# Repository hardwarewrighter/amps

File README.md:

# Amplifier bench projects

This repository collects small audio amplifier circuits, SPICE simulations, and bench build guides. The first hardware build is a 5 V mono amplifier with an LM358P driving a 2N2222/2N2907-family push-pull output stage. It has a board-mounted volume control and an eight-pin interface shared with a wired PAM8403-style carrier. The mono build uses the left channel. The harness provides separate speaker returns for a future stereo board.

## Start with the 2N2222 amplifier

The [build guide](circuits/2n2222/index.html) includes the parts list, breadboard layout, bench test steps, and both sides of the single-sided through-hole PCB. Open it directly in a browser or serve it from the repository root.

```sh
python -m http.server 8765 --bind 127.0.0.1 --directory circuits/2n2222
```

Open [http://localhost:8765/](http://localhost:8765/). Start with the 8.2 Ω dummy load, then repeat the bench checks after soldering. The PCB has passed KiCad design rule checks. The build guide gives simulated reference values for the physical tests.

- [KiCad PCB](circuits/2n2222/push-pull.kicad_pcb)
- [SPICE model](circuits/2n2222/push-pull.cir), runnable with `ngspice -b circuits/2n2222/push-pull.cir`

## Documentation and reference designs

- [Experiment plan](docs/plan.md) for comparing transistor pairs, op-amp drivers, and integrated amplifiers.
- [Research notes](docs/research.txt) and [follow-up notes](docs/research2.txt) for the design background.
- [Netlist notes](net/NOTES.txt) and [amplifier choices](net/CHOICES.txt) for model assumptions and circuit options.
- [Parts lists](bom/README.txt) and [simulation comparison](reports/index.html).
- [LM386 reference build](circuits/lm386-simple/README.txt) and [tone-control tool](tools/tone-control/README.txt).
- [Change history](CHANGES.md).

## Copyright and license

Copyright (c) 2026 Michael A Wright. See [COPYRIGHT](COPYRIGHT).

The project is licensed under the [MIT License](LICENSE).

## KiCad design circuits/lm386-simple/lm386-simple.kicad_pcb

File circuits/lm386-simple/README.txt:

Open lm386-simple.kicad_sch in KiCad Schematic Editor, or open
lm386-simple.kicad_pro in the KiCad project manager.

All ten physical components are placed and wired. KiCad 10.0.7 ERC:
zero errors, zero warnings. Exported pin connectivity was checked against
the intended circuit, including the positive side of C4 facing U1 pin 5.

lm386-simple.pdf is the printable schematic.
lm386-simple.kicad_pcb is a placed, UNROUTED learning board with footprints
and net connections. It is not ready for fabrication. Footprints are
provisional; check sizes against your actual capacitors/connectors first.
Use Update PCB from Schematic (F8) after editing the schematic.

This drawing uses 220uF output coupling and 47nF in the RC network, standard
values replacing 250uF/50nF in the earlier netlist. C3 and C4 are polarized.
Pins 1/7/8 are intentionally open. Supply is single +6 V; load is an external
8-ohm speaker at J3. This has no volume control; start with a small input.

The graphical project is for drawing/PCB exploration. Simulation sources
and a KiCad simulation model have not been attached to its symbols.
For the corresponding standalone ngspice example, run:
  ngspice circuits/lm386-simple/lm386-simple.cir
That uses the same approximate educational model as the earlier LM386 deck;
it does not validate power, distortion, stability or thermal performance.

Project-local library tables refer to the installed Arch KiCad libraries.
Embedded symbols allow the schematic to display without external symbols.

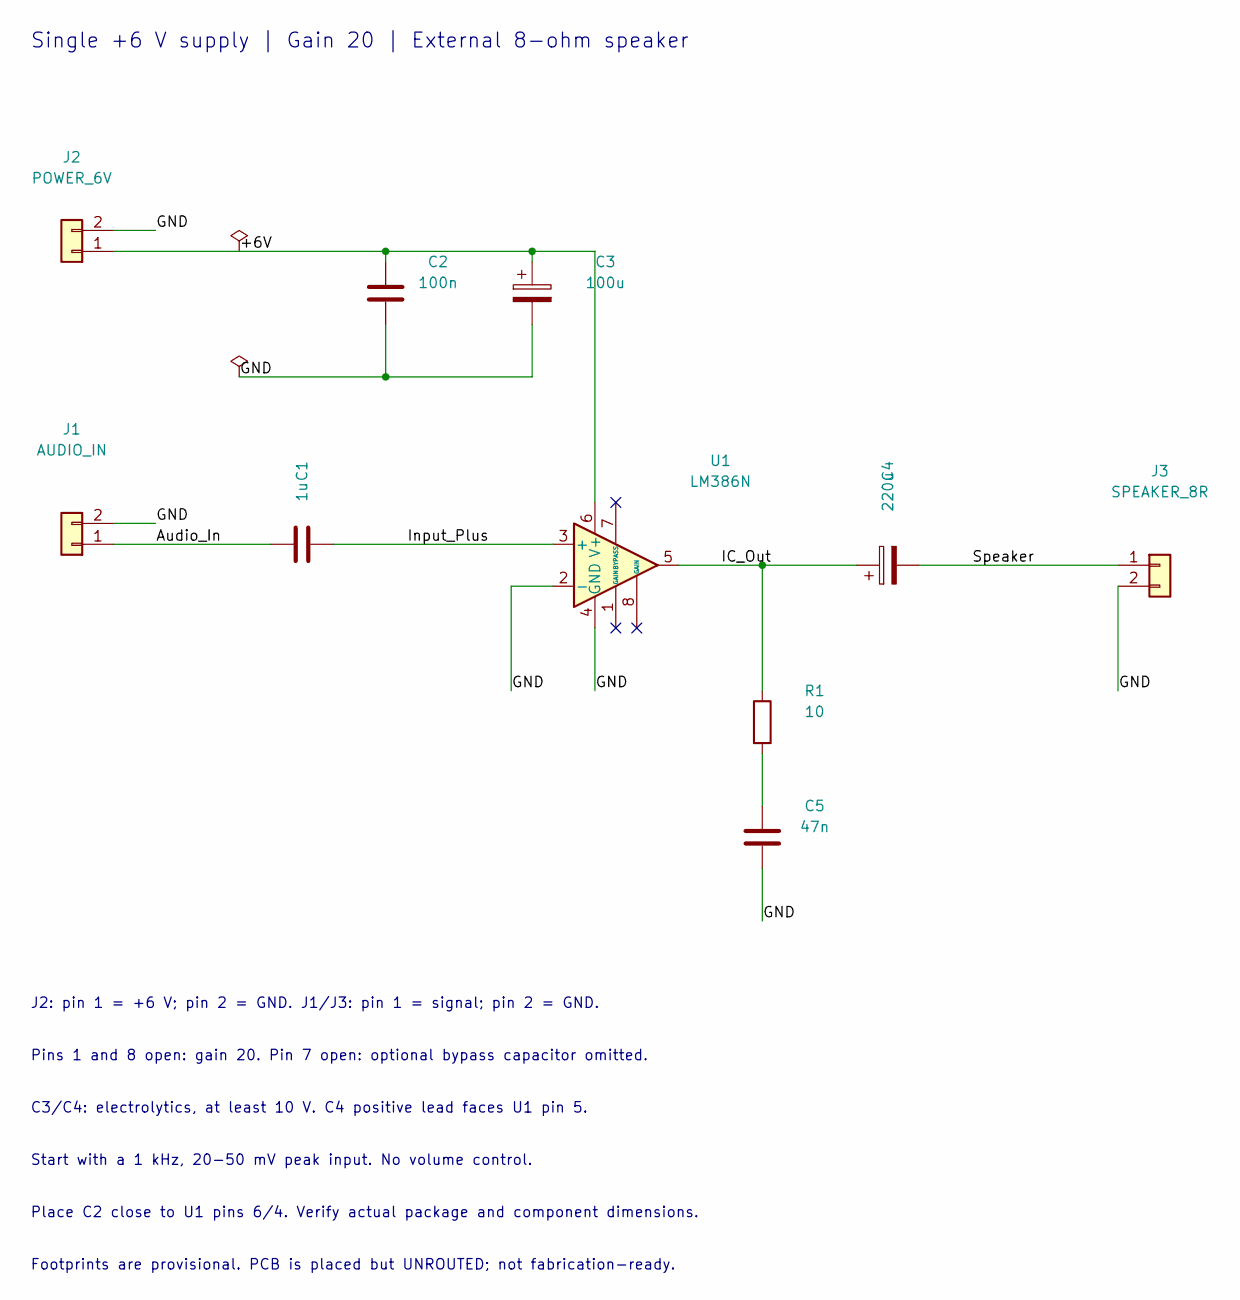
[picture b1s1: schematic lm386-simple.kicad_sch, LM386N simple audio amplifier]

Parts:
C1: 1u; C_Disc_D5.0mm_W2.5mm_P5.00mm
C2: 100n; C_Disc_D5.0mm_W2.5mm_P5.00mm
C3: 100u; CP_Radial_D6.3mm_P2.50mm
C4: 220u; CP_Radial_D6.3mm_P2.50mm
C5: 47n; C_Disc_D5.0mm_W2.5mm_P5.00mm
J1: AUDIO_IN; PinHeader_1x02_P2.54mm_Vertical
J2: POWER_6V; PinHeader_1x02_P2.54mm_Vertical
J3: SPEAKER_8R; PinHeader_1x02_P2.54mm_Vertical
R1: 10; R_Axial_DIN0207_L6.3mm_D2.5mm_P7.62mm_Horizontal
U1: LM386N; DIP-8_W7.62mm

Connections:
/+6V: C2.1, C3.1, J2.1, U1.6 (V+)
/Audio_In: C1.1, J1.1
/GND: C2.2, C3.2, C5.2, J1.2, J2.2, J3.2, U1.2 (-), U1.4 (GND)
/IC_Out: C4.1, R1.1, U1.5
/Input_Plus: C1.2, U1.3 (+)
/Speaker: C4.2, J3.1
unnamed: C5.1, R1.2

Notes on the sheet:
Single +6 V supply | Gain 20 | External 8-ohm speaker
J2: pin 1 = +6 V; pin 2 = GND. J1/J3: pin 1 = signal; pin 2 = GND.
Pins 1 and 8 open: gain 20. Pin 7 open: optional bypass capacitor omitted.
C3/C4: electrolytics, at least 10 V. C4 positive lead faces U1 pin 5.
Start with a 1 kHz, 20-50 mV peak input. No volume control.
Place C2 close to U1 pins 6/4. Verify actual package and component dimensions.
Footprints are provisional. PCB is placed but UNROUTED; not fabrication-ready.

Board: 2 copper layers, 10 parts (0 on the bottom side), 7 nets, no tracks yet.

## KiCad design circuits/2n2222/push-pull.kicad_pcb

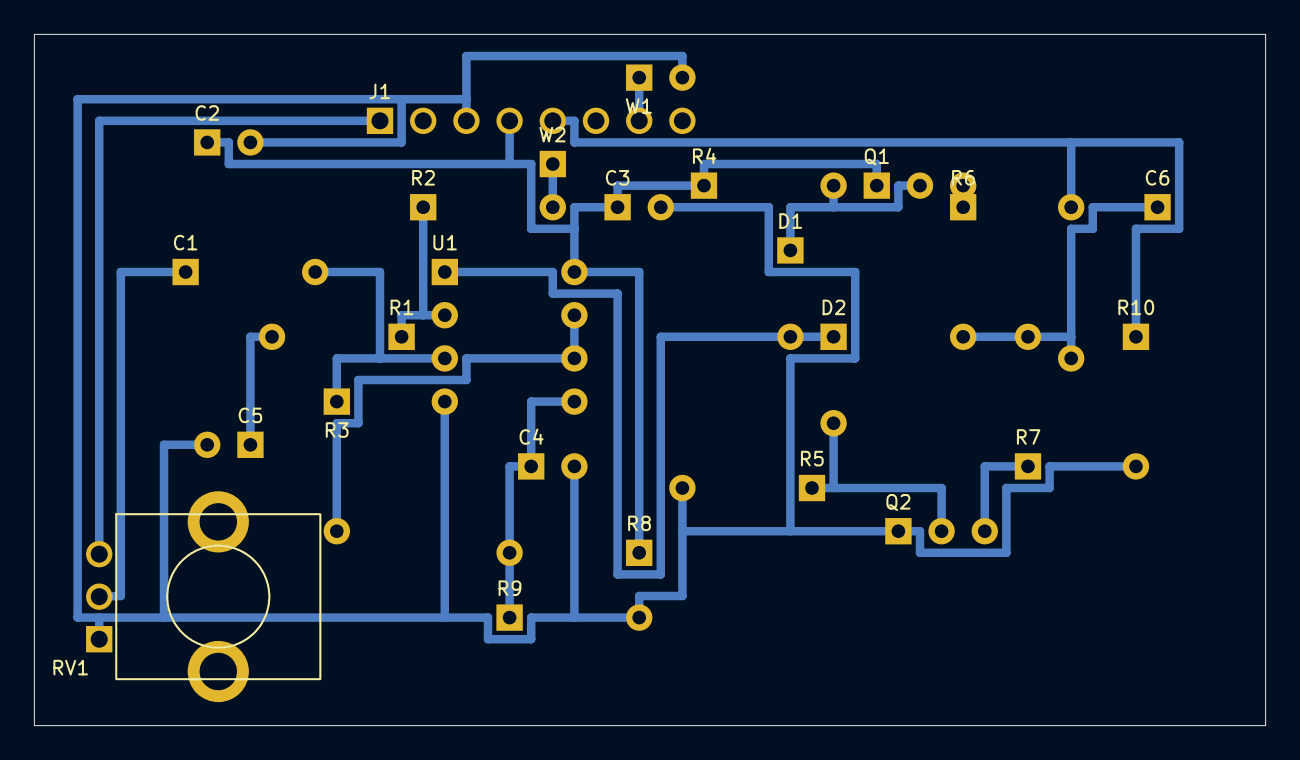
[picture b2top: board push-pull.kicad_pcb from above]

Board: 2 copper layers, 72.4 x 40.6 mm, 25 parts (0 on the bottom side), 18 nets.

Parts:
C1: C1
C2: C2
C3: C3
C4: C4
C5: C5
C6: C6
D1: D1
D2: D2
J1: J1
Q1: Q1
Q2: Q2
R1: R1
R2: R2
R3: R3
R4: R4
R5: R5
R6: R6
R7: R7
R8: R8
R9: R9
R10: R10
RV1: RV1
U1: U1
W1: W1
W2: W2

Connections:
+5: C2.1, C3.1, J1.4, Q1.1, R4.1, R8.1, U1.8
ACREF: C5.1, R1.2
BN: D1.1, Q1.2, R4.2
BP: D2.2, Q2.2, R5.1
BUF: R3.2, U1.6, U1.7
DRV: D1.2, D2.1, U1.1
EN: Q1.3, R6.1
EP: Q2.3, R7.1
FB: R1.1, R2.1, U1.2
GND: C2.2, C3.2, C4.2, C5.2, J1.3, Q2.1, R5.2, R9.2, R10.2, RV1.1, U1.4, W1.2
L+: C6.2, J1.5, R10.1
L-: J1.7, W1.1
LIN: J1.1, RV1.3
MID: C4.1, R8.2, R9.1, U1.5
OUT: C6.1, R6.2, R7.2, W2.2
PLUS: C1.2, R3.1, U1.3
SENSE: R2.2, W2.1
VOL: C1.1, RV1.2

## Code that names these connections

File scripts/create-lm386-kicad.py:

#!/usr/bin/env python3
"""Generate the LM386 learning schematic from installed KiCad library symbols."""
from pathlib import Path
import json
import math
import re
import uuid

ROOT=Path(__file__).resolve().parent.parent
OUT=ROOT/'circuits/lm386-simple'
OUT.mkdir(parents=True,exist_ok=True)
NAME='lm386-simple'
uid=lambda: str(uuid.uuid4())
q=lambda s: json.dumps(str(s))
root_uuid=uid()

def extract(library,name):
    data=Path('/usr/share/kicad/symbols',library+'.kicad_sym').read_text()
    start=data.index('(symbol '+q(name)+'\n')
    depth=0; quoted=False; escaped=False
    for i in range(start,len(data)):
        c=data[i]
        if quoted:
            if escaped: escaped=False
            elif c=='\\': escaped=True
            elif c=='"': quoted=False
        elif c=='"': quoted=True
        elif c=='(': depth+=1
        elif c==')':
            depth-=1
            if depth==0:
                return data[start:i+1].replace('(symbol '+q(name), '(symbol '+q(library+':'+name),1)
    raise ValueError(name)

libraries=[('Amplifier_Audio','LM386'),('Device','C'),('Device','C_Polarized'),('Device','R'),('Connector_Generic','Conn_01x02'),('power','PWR_FLAG')]
lib={f'{a}:{b}':extract(a,b) for a,b in libraries}
parts=[];items=[]

def prop(name,value,x,y,hidden=False):
    return f'(property {q(name)} {q(value)} (at {x:g} {y:g} 0) (effects (font (size 1.27 1.27))'+(' (hide yes)' if hidden else '')+'))'

def symbol(lib_id,ref,value,x,y,angle=0,footprint='',label_x=None,label_y=None):
    ident=uid(); lx=x+6.35 if label_x is None else label_x; ly=y-3.81 if label_y is None else label_y
    pins=re.findall(r'\(number "([^"]+)"',lib[lib_id])
    items.append(f'''(symbol (lib_id {q(lib_id)}) (at {x:g} {y:g} {angle}) (unit 1)
(exclude_from_sim {'yes' if ref.startswith('J') else 'no'}) (in_bom {'no' if ref.startswith('#') else 'yes'}) (on_board {'no' if ref.startswith('#') else 'yes'}) (dnp no) (uuid "{ident}")
{prop('Reference',ref,lx,ly,ref.startswith('#'))}
{prop('Value',value,lx,ly+2.54,ref.startswith('#'))}
{prop('Footprint',footprint,x,y,True)}
{''.join(f'(pin {q(pin)} (uuid "{uid()}"))' for pin in pins)}
(instances (project "{NAME}" (path "/{root_uuid}" (reference {q(ref)}) (unit 1)))))''')
    parts.append(dict(ref=ref,value=value,lib_id=lib_id,x=x,y=y,angle=angle,footprint=footprint,uuid=ident))

def wire(*pts):
    for a,b in zip(pts,pts[1:]):
        assert a!=b
        items.append(f'(wire (pts (xy {a[0]:g} {a[1]:g}) (xy {b[0]:g} {b[1]:g})) (stroke (width 0) (type default)) (uuid "{uid()}"))')

def label(name,x,y):
    items.append(f'(label {q(name)} (at {x:g} {y:g} 0) (effects (font (size 1.27 1.27)) (justify left bottom)) (uuid "{uid()}"))')

def junction(x,y):
    items.append(f'(junction (at {x:g} {y:g}) (diameter 0) (color 0 0 0 0) (uuid "{uid()}"))')

def text(s,x,y,size=1.27):
    items.append(f'(text {q(s)} (at {x:g} {y:g} 0) (effects (font (size {size} {size})) (justify left)) (uuid "{uid()}"))')

def nc(x,y):
    items.append(f'(no_connect (at {x:g} {y:g}) (uuid "{uid()}"))')

DIP='Package_DIP:DIP-8_W7.62mm'
CAP='Capacitor_THT:C_Disc_D5.0mm_W2.5mm_P5.00mm'
EL='Capacitor_THT:CP_Radial_D6.3mm_P2.50mm'
CON='Connector_PinHeader_2.54mm:PinHeader_1x02_P2.54mm_Vertical'
symbol('Amplifier_Audio:LM386','U1','LM386N',127,88.9,footprint=DIP,label_x=139.7,label_y=76.2)
symbol('Device:C','C1','1u',88.9,86.36,90,CAP,label_x=88.9,label_y=77.47)
symbol('Device:C','C2','100n',99.06,55.88,footprint=CAP)
symbol('Device:C_Polarized','C3','100u',116.84,55.88,footprint=EL,label_x=125.73)
symbol('Device:C_Polarized','C4','220u',160.02,88.9,90,EL,label_x=160.02,label_y=77.47)
symbol('Device:R','R1','10',144.78,107.95,footprint='Resistor_THT:R_Axial_DIN0207_L6.3mm_D2.5mm_P7.62mm_Horizontal')
symbol('Device:C','C5','47n',144.78,121.92,footprint=CAP)
symbol('Connector_Generic:Conn_01x02','J1','AUDIO_IN',60.96,86.36,180,CON,label_x=60.96,label_y=72.39)
symbol('Connector_Generic:Conn_01x02','J2','POWER_6V',60.96,50.8,180,CON,label_x=60.96,label_y=39.37)
symbol('Connector_Generic:Conn_01x02','J3','SPEAKER_8R',193.04,88.9,0,CON,label_x=193.04,label_y=77.47)
symbol('power:PWR_FLAG','#FLG01','PWR_FLAG',81.28,50.8)
symbol('power:PWR_FLAG','#FLG02','PWR_FLAG',81.28,66.04)
# Supply rail and bypass capacitors.
wire((66.04,50.8),(81.28,50.8),(99.06,50.8),(116.84,50.8),(124.46,50.8),(124.46,81.28))
wire((66.04,48.26),(71.12,48.26));label('GND',71.12,48.26)
label('+6V',81.28,50.8)
wire((99.06,50.8),(99.06,52.07));junction(99.06,50.8)
wire((116.84,50.8),(116.84,52.07));junction(116.84,50.8)
wire((99.06,59.69),(99.06,66.04));wire((116.84,59.69),(116.84,66.04),(99.06,66.04),(81.28,66.04))
label('GND',81.28,66.04);junction(99.06,66.04)
# Input path and ground return.
wire((66.04,86.36),(85.09,86.36));label('Audio_In',71.12,86.36)
wire((92.71,86.36),(119.38,86.36));label('Input_Plus',101.6,86.36)
wire((66.04,83.82),(71.12,83.82));label('GND',71.12,83.82)
wire((119.38,91.44),(114.3,91.44),(114.3,104.14));label('GND',114.3,104.14)
wire((124.46,96.52),(124.46,104.14));label('GND',124.46,104.14)
for point in [(127,96.52),(129.54,96.52),(127,81.28)]: nc(*point)
# Output and stabilization network.
wire((134.62,88.9),(144.78,88.9),(156.21,88.9));junction(144.78,88.9);label('IC_Out',139.7,88.9)
wire((163.83,88.9),(187.96,88.9));label('Speaker',170.18,88.9)
wire((187.96,91.44),(187.96,104.14));label('GND',187.96,104.14)
wire((144.78,88.9),(144.78,104.14));wire((144.78,111.76),(144.78,118.11));wire((144.78,125.73),(144.78,132.08));label('GND',144.78,132.08)
text('Single +6 V supply | Gain 20 | External 8-ohm speaker',55.88,25.4,1.8)
text('J2: pin 1 = +6 V; pin 2 = GND. J1/J3: pin 1 = signal; pin 2 = GND.',55.88,142.24)
text('Pins 1 and 8 open: gain 20. Pin 7 open: optional bypass capacitor omitted.',55.88,148.59)
text('C3/C4: electrolytics, at least 10 V. C4 positive lead faces U1 pin 5.',55.88,154.94)
text('Start with a 1 kHz, 20-50 mV peak input. No volume control.',55.88,161.29)
text('Place C2 close to U1 pins 6/4. Verify actual package and component dimensions.',55.88,167.64)
text('Footprints are provisional. PCB is placed but UNROUTED; not fabrication-ready.',55.88,173.99)
schematic=f'''(kicad_sch (version 20250114) (generator "eeschema") (uuid "{root_uuid}") (paper "A4")
(title_block (title "LM386N simple audio amplifier") (date "2026-10-26") (rev "A") (comment 1 "Educational project: single +6 V, gain 20"))
(lib_symbols {' '.join(lib.values())})
{' '.join(items)}
(sheet_instances (path "/" (page "1")))
(embedded_fonts no))'''
(OUT/(NAME+'.kicad_sch')).write_text(schematic)
(OUT/(NAME+'.kicad_pro')).write_text(json.dumps({'meta':{'filename':NAME+'.kicad_pro','version':1},'net_settings':{'classes':[{'name':'Default','clearance':0.25,'track_width':0.4,'via_diameter':0.8,'via_drill':0.4}],'meta':{'version':3}}},indent=2)+'\n')
(OUT/'components.json').write_text(json.dumps({'root_uuid':root_uuid,'parts':parts},indent=2)+'\n')
print(OUT/(NAME+'.kicad_sch'))

# Project-local library tables make checks independent of first-run GUI setup.
(OUT/'sym-lib-table').write_text('(sym_lib_table (version 7)\n'+''.join(f'(lib (name "{a}") (type "KiCad") (uri "/usr/share/kicad/symbols/{a}.kicad_sym") (options "") (descr ""))\n' for a in dict(libraries))+')\n')
fp_libs=['Package_DIP','Capacitor_THT','Connector_PinHeader_2.54mm','Resistor_THT']
(OUT/'fp-lib-table').write_text('(fp_lib_table (version 7)\n'+''.join(f'(lib (name "{a}") (type "KiCad") (uri "/usr/share/kicad/footprints/{a}.pretty") (options "") (descr ""))\n' for a in fp_libs)+')\n')
